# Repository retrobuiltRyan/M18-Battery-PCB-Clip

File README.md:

# M18-Battery-PCB-Clip
Clip-on PCBs with spade terminals compatible with Milwaukee M18 battery packs. 
https://youtu.be/rkWTQf_fx88

BoM to build whats in video. 

|Item	|Description	|P/N	|$/ Each |	Qty|	Line Total|	Vendor	Notes|
|-----|-------------|-----|---------|----|------------|--------------------|
|1|	Battery Spade-Board (PCB to Board solder)|	A100452CT-ND	|0.084	|2|	0.168|	DigiKey	|
|2|	FUSE CLIP BLADE 500V 30A PCB	|36-3557-ND|	0.24|	2|	0.48|	DigiKey	|
|3|	M3 Threaded Insert	|94459A130	|0.275|	2	|0.55|	McMaster|	
|4|	LED 1208	|na	|0.1	|1|	0.1|	DigiKey	optional|
|5|	3.3K Resistor LED 1208|	na|	0.1|	1	|0.1|	DigiKey	optional|
|6|	FUSE AUTO 2A 32VDC BLADE ATO/ATC|	F4192-ND|	0.38|	1|	1|	DigiKey	example 2Amp|
|7|	TERM BLK 2POS SIDE ENT 3.5MM PCB|	732-2747-ND|	0.88	|2	|1.76|	DigiKey	|

Total Cost 4.16

Some ATC fuses with increasing amp rating (digikey P/N) for reference. Do not take this as a suggestion to push this much current through this PCB! 
| PN | Amperage| notes|
|----|---------|------|
|F4191-ND| 1 amp| |
|F4192-ND| 2 amp| |
|F4193-ND| 3 amp| |
|F4194-ND| 4 amp| I would not exceed this unless you  monitor temp and duration. |
|F4197-ND| 5 amp| risky|
|F4198-ND| 7.5 amp| uh, not confident on this|
|F4199-ND| 10 amp| haha I do not think 1oz copper will survive|

Safety Claim here: Do not use your batteries in any way outside what the manufacturer claims.

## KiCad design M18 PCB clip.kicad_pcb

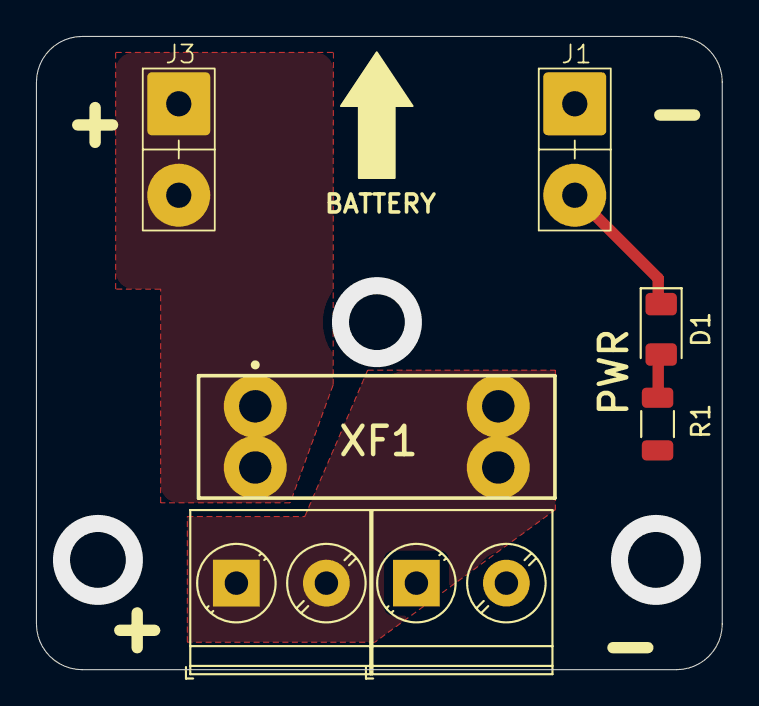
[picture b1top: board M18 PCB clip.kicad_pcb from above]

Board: 2 copper layers, 38.1 x 35.2 mm, 7 parts (0 on the bottom side), 4 nets.

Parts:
D1: D; D_1206_3216Metric
J1, J3: CONN QC TAB 0.250 SOLDER
J2, J5: Screw_Terminal_2_P5.00mm; TerminalBlock_Phoenix_PT-1,5-2-5.0-H_1x02_P5.00mm_Horizontal
R1: R_US; R_1206_3216Metric
XF1: 3557-2; FUSE CLIP BLADE 500V 30A PCB

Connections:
/VFuse: J5.1, J5.2, R1.1, XF1.3, XF1.4
GND: D1.1 (K), J1.1, J1.2, J2.1, J2.2
unnamed: D1.2 (A), R1.2
VCC: J3.1, J3.2, XF1.1, XF1.2

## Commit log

2024-10-27 Add files via upload
    Some older 3D printer might need this model scaled +1% X & Y to accommodate PLA shrinkage.
2024-11-01 Update README.md
    Extra ATC fuse P/Ns added
2024-11-01 Update README.md
    table zed the BoM
2024-12-15 Some tolerances adjustment for older printers
    Print 100% scale on a good printer (X1C)
    Print 101% X on older, not as a great printer (Ender 3)
    Assumes PLA material for both.
2024-12-16 M3 TF screw
    Thread Forming M3 screws for plastic. More economical (parts, labor) vs. threaded inserted and M3 machine screws.
2024-12-16 Alignment clip for battery
    Alignment clip for battery (optional, but nice). Requires 3D printing and M3 threaded inserts with M3x6mm screws.
2025-01-03 Safety Clip (bumper)
    Cover those live terminals because it might be a problem if not insulated.
2025-01-03 Update README.md
    added warning "do not do this"
2025-01-03 Update README.md
    youtube link updated
2025-09-19 PCB design files (kicad v8.x)
2025-09-19 CAD design files (solidworks 2024 )
